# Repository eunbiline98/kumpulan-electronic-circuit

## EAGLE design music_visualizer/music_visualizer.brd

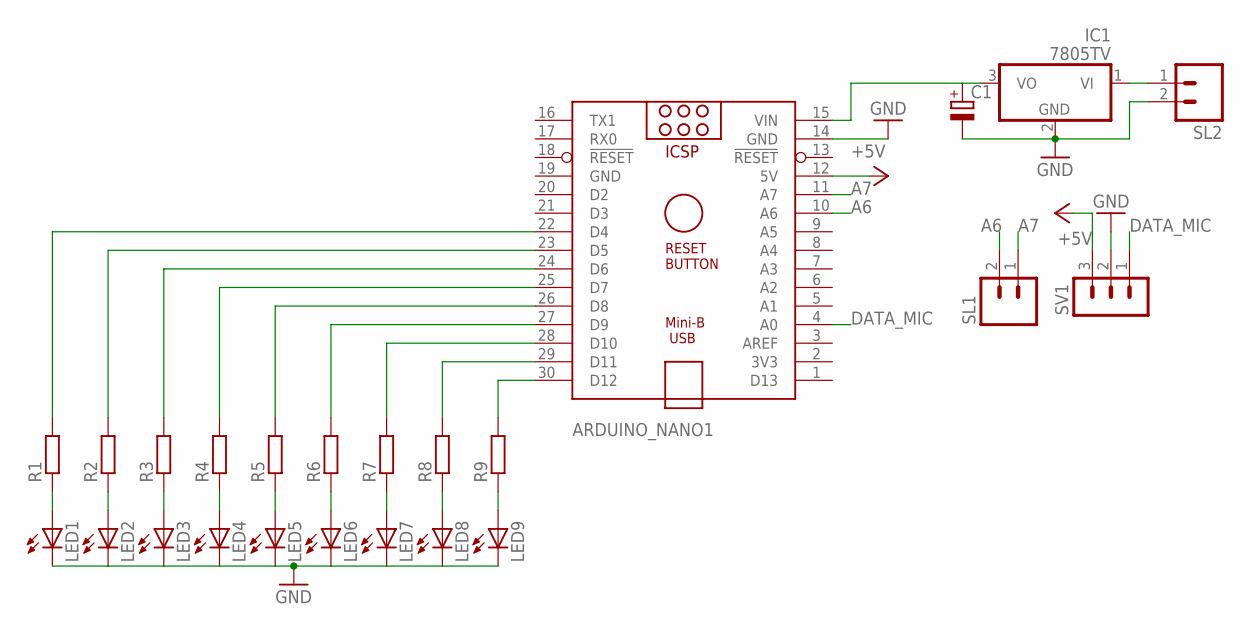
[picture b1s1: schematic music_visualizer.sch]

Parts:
ARDUINO_NANO1: ARDUINO_NANO
C1: CPOL-EUE2.5-7; E2,5-7
IC1: 7805TV; TO220V
LED1, LED2, LED3, LED4, LED5, LED6, LED7, LED8, LED9: LED5MM
R1, R2, R3, R4, R5, R6, R7, R8, R9: R-EU_0207/10; 0207/10
SL1, SL2: M02; 02P
SV1: MA03-1

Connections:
+5V: ARDUINO_NANO1.12 (5V), SV1.3
A6: ARDUINO_NANO1.10 (A6), SL1.2
A7: ARDUINO_NANO1.11 (A7), SL1.1
DATA_MIC: ARDUINO_NANO1.4 (A0), SV1.1
GND: ARDUINO_NANO1.14 (GND), ARDUINO_NANO1.19 (GND), C1.-, IC1.2 (GND), LED1.K (C), LED2.K (C), LED3.K (C), LED4.K (C), LED5.K (C), LED6.K (C), LED7.K (C), LED8.K (C), LED9.K (C), SL2.2, SV1.2
unnamed: LED1.A, R1.1
unnamed: ARDUINO_NANO1.30 (D12), R9.2
unnamed: ARDUINO_NANO1.29 (D11), R8.2
unnamed: ARDUINO_NANO1.28 (D10), R7.2
unnamed: ARDUINO_NANO1.27 (D9), R6.2
unnamed: ARDUINO_NANO1.26 (D8), R5.2
unnamed: ARDUINO_NANO1.25 (D7), R4.2
unnamed: ARDUINO_NANO1.24 (D6), R3.2
unnamed: ARDUINO_NANO1.23 (D5), R2.2
unnamed: ARDUINO_NANO1.22 (D4), R1.2
unnamed: LED2.A, R2.1
unnamed: LED3.A, R3.1
unnamed: LED4.A, R4.1
unnamed: LED5.A, R5.1
unnamed: LED6.A, R6.1
unnamed: LED7.A, R7.1
unnamed: LED8.A, R8.1
unnamed: LED9.A, R9.1
unnamed: ARDUINO_NANO1.15 (VIN), C1.+, IC1.3 (VO)
unnamed: IC1.1 (VI), SL2.1

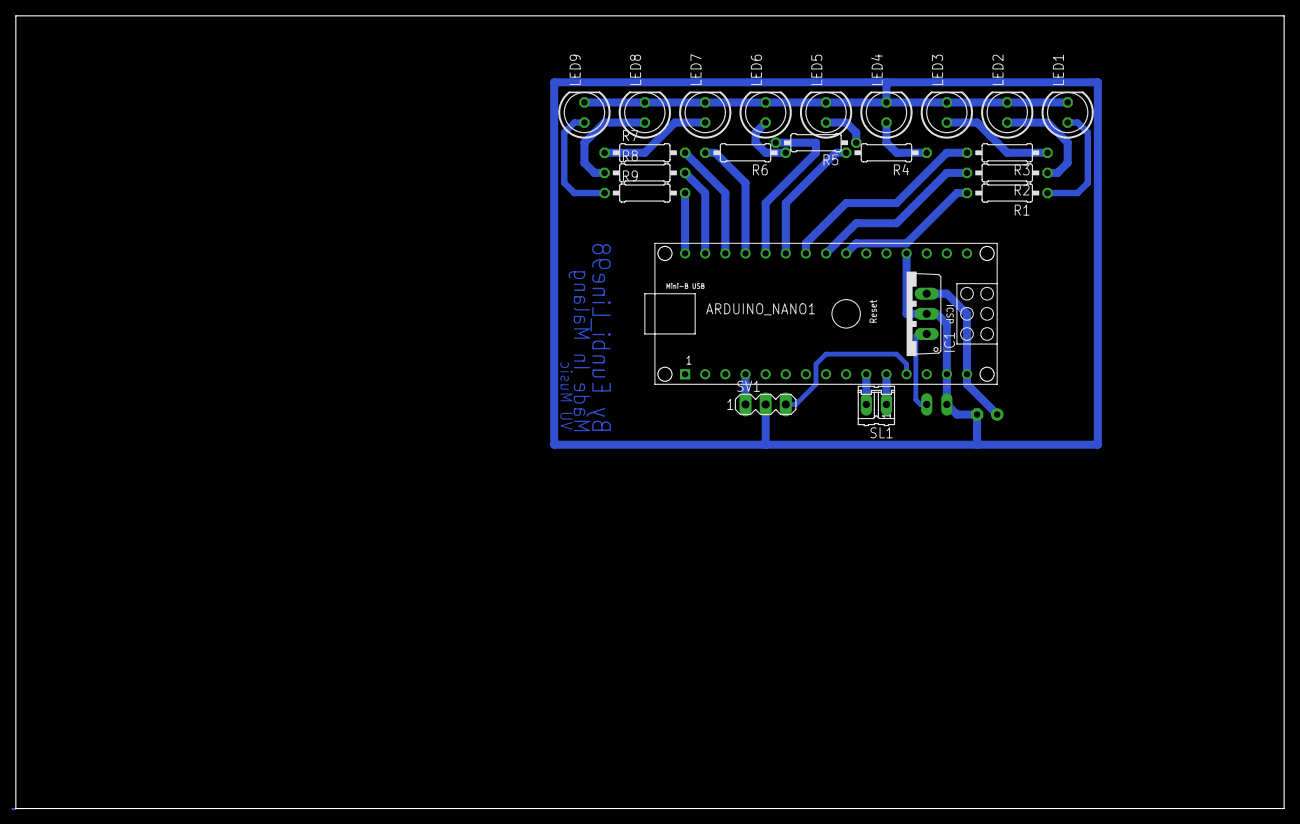
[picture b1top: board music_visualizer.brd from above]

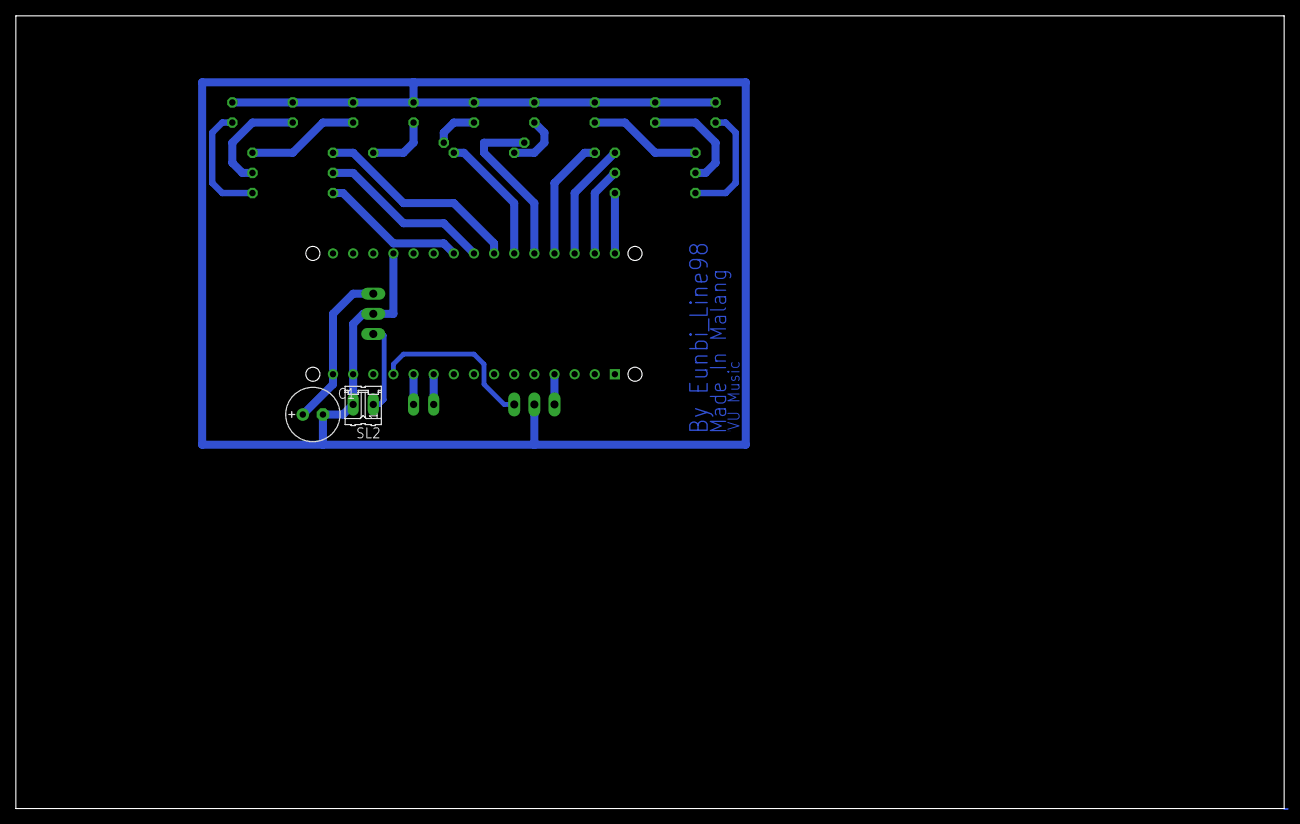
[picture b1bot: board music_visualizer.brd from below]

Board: 2 copper layers, 160.0 x 100.0 mm, 24 parts (2 on the bottom side), 25 nets.

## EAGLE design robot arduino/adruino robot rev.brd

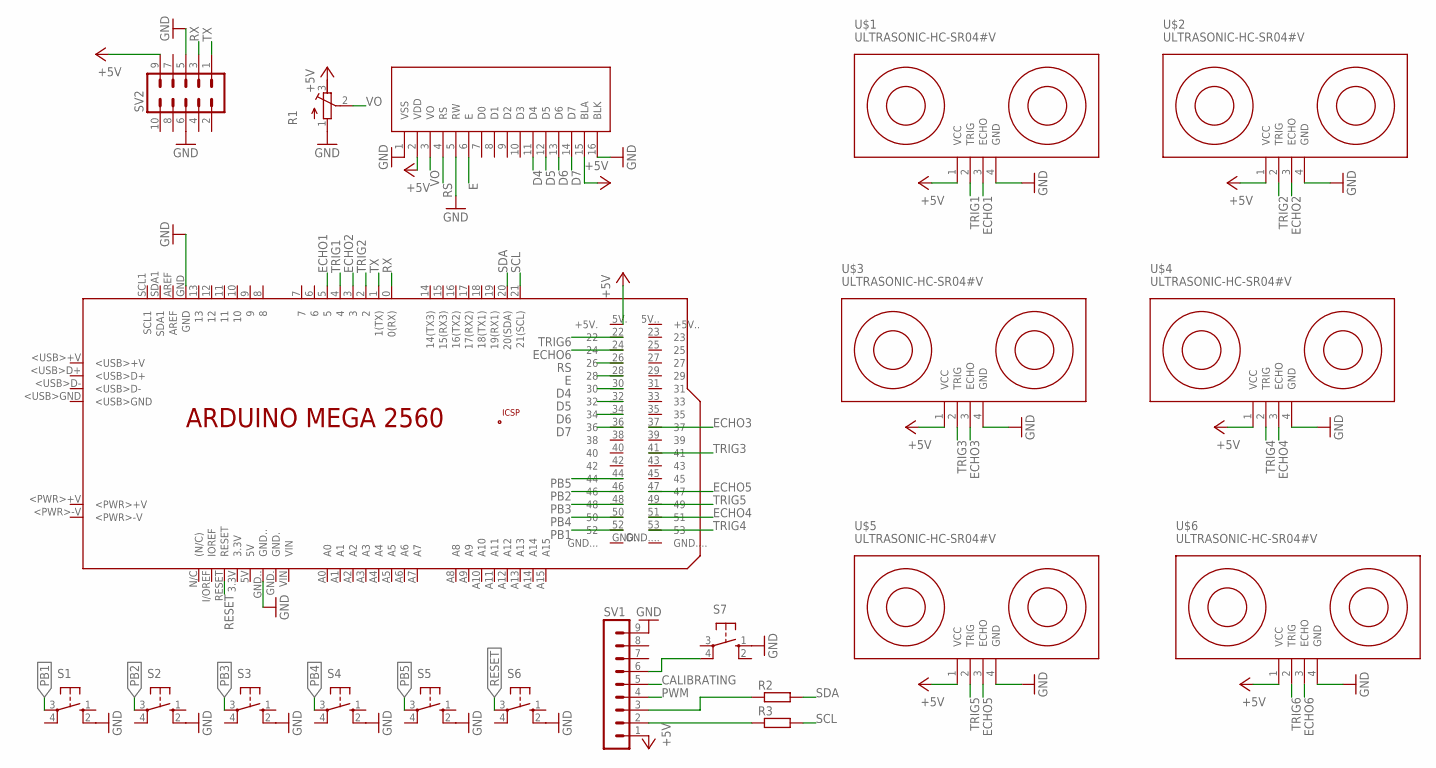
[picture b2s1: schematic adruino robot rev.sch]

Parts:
PCB1: ARDUINO_MEGA2560
R1: R-TRIMM3339P; RTRIM3339P
R2, R3: R-EU_0204/7; 0204/7
S1, S2, S3, S4, S5, S6, S7: 40-XX; B3F-40XX
SV1: MA09-1
SV2: ML10
U$1, U$2, U$3, U$4, U$5, U$6: ULTRASONIC-HC-SR04#V
U$7: 2X16LCDTOP

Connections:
+5V: PCB1.5V. (+5V.), R1.3 (E), SV1.1, SV2.9, U$1.1 (VCC), U$2.1 (VCC), U$3.1 (VCC), U$4.1 (VCC), U$5.1 (VCC), U$6.1 (VCC), U$7.2 (VDD), U$7.15 (BLA)
CALIBRATING: SV1.5
D4: PCB1.30, U$7.11 (D4)
D5: PCB1.32, U$7.12 (D5)
D6: PCB1.34, U$7.13 (D6)
D7: PCB1.36, U$7.14 (D7)
E: PCB1.28, U$7.6 (E)
ECHO1: PCB1.5, U$1.3 (ECHO)
ECHO2: PCB1.3, U$2.3 (ECHO)
ECHO3: PCB1.37, U$3.3 (ECHO)
ECHO4: PCB1.51, U$4.3 (ECHO)
ECHO5: PCB1.47, U$5.3 (ECHO)
ECHO6: PCB1.24, U$6.3 (ECHO)
GND: PCB1.GND, PCB1.GND.., R1.1 (A), S1.2 (S1), S2.2 (S1), S3.2 (S1), S4.2 (S1), S5.2 (S1), S6.2 (S1), S7.1 (S), SV1.9, SV2.5, SV2.6, U$1.4 (GND), U$2.4 (GND), U$3.4 (GND), U$4.4 (GND), U$5.4 (GND), U$6.4 (GND), U$7.1 (VSS), U$7.5 (RW), U$7.16 (BLK)
unnamed: R2.1, SV1.3
unnamed: R3.1, SV1.2
unnamed: S7.4 (P1), SV1.6
PB1: PCB1.52, S1.3
PB2: PCB1.46, S2.3
PB3: PCB1.48, S3.3
PB4: PCB1.50, S4.3
PB5: PCB1.44, S5.3
PWM: SV1.4
RESET: PCB1.RESET, S6.3
RS: PCB1.26, U$7.4 (RS)
RX: PCB1.0 (0(RX)), SV2.3
SCL: PCB1.21 (21(SCL)), R3.2
SDA: PCB1.20 (20(SDA)), R2.2
TRIG1: PCB1.4, U$1.2 (TRIG)
TRIG2: PCB1.2, U$2.2 (TRIG)
TRIG3: PCB1.41, U$3.2 (TRIG)
TRIG4: PCB1.53, U$4.2 (TRIG)
TRIG5: PCB1.49, U$5.2 (TRIG)
TRIG6: PCB1.22, U$6.2 (TRIG)
TX: PCB1.1 (1(TX)), SV2.1
VO: R1.2 (S), U$7.3 (VO)

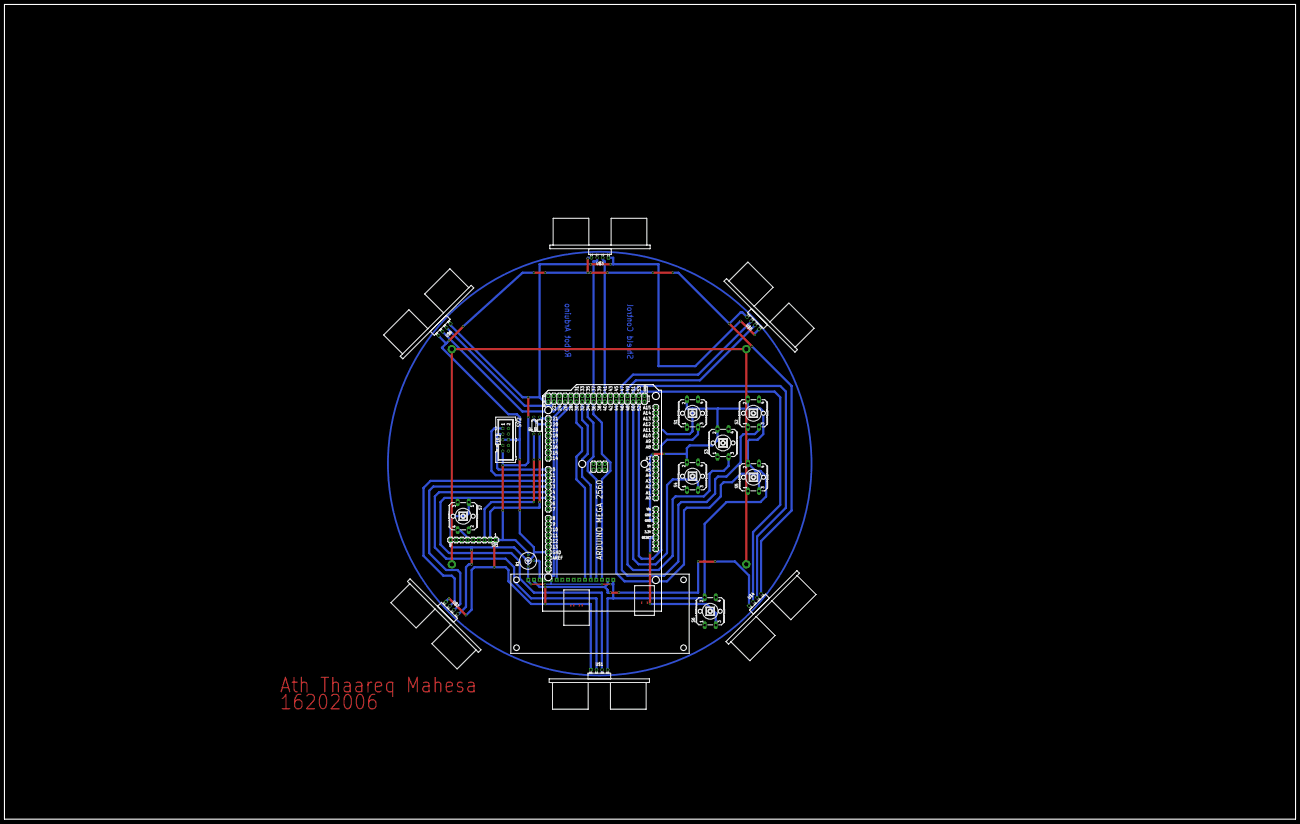
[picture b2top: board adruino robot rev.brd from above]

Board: 2 copper layers, 579.1 x 365.4 mm, 20 parts (0 on the bottom side), 34 nets.

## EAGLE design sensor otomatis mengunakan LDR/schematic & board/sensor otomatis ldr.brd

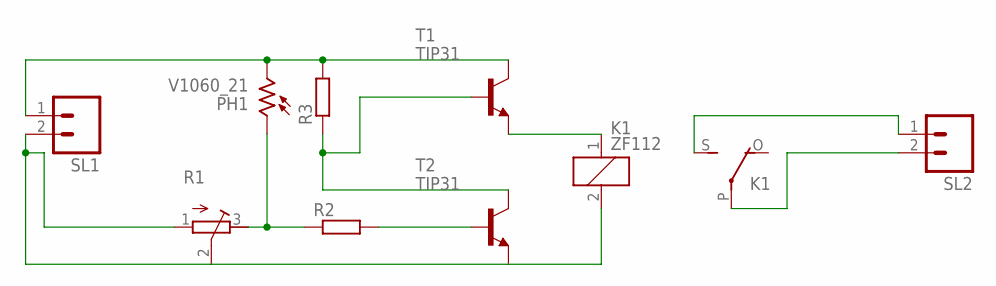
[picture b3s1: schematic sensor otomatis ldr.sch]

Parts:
K1: ZF112
PH1: V1060_21; TO-5_V10
R1: R-TRIMM3339P; RTRIM3339P
R2, R3: R-EU_0207/10; 0207/10
SL1, SL2: M02; 02P
T1, T2: TIP31; TO220

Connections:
unnamed: PH1.2, R3.2, SL1.1, T1.2 (C)
unnamed: K1.1, T1.3 (E)
unnamed: R2.2, T2.1 (B)
unnamed: PH1.1, R1.3 (E), R2.1
unnamed: R3.1, T1.1 (B), T2.2 (C)
unnamed: K1.2, R1.1 (A), R1.2 (S), SL1.2, T2.3 (E)
unnamed: K1.P, SL2.2
unnamed: K1.S, SL2.1

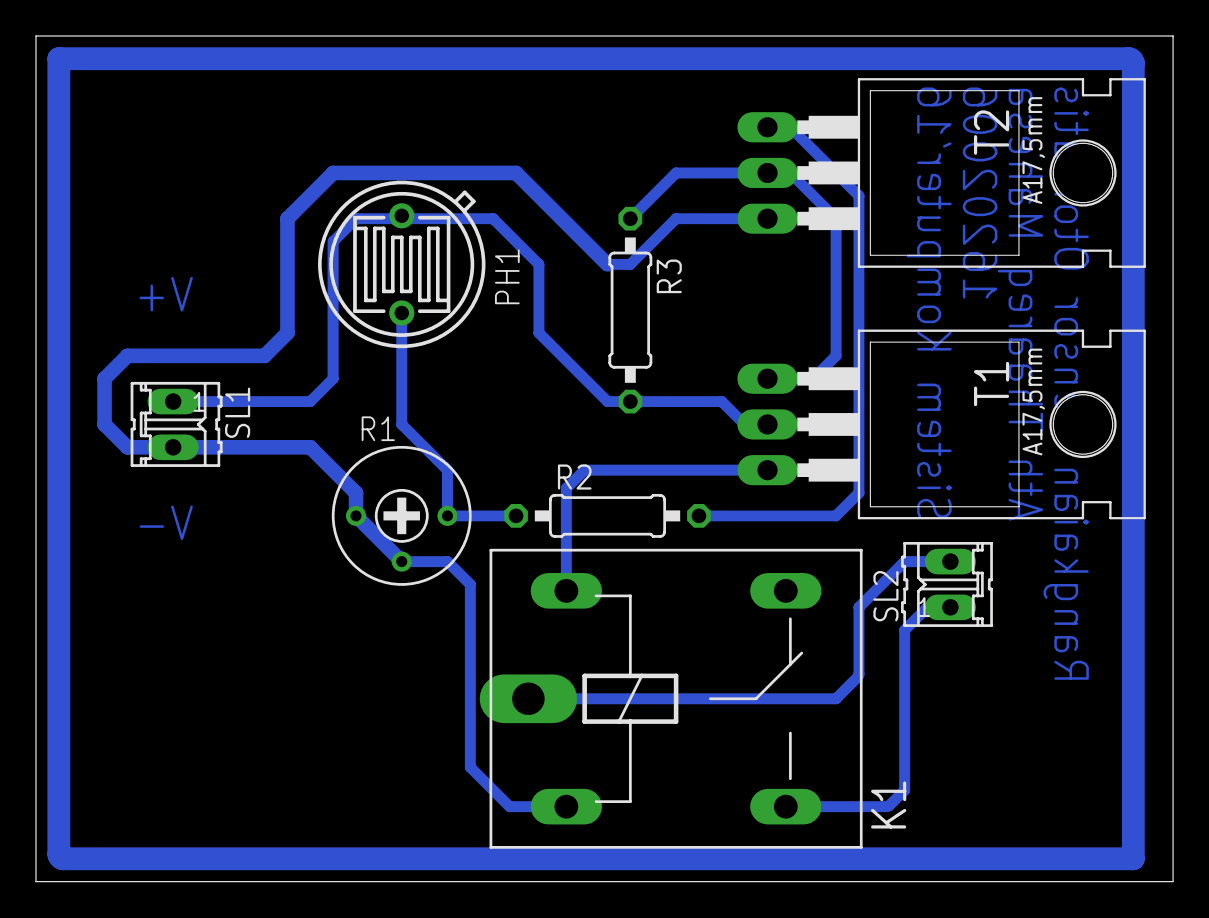
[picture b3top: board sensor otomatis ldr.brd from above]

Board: 2 copper layers, 63.2 x 47.0 mm, 9 parts (0 on the bottom side), 8 nets.

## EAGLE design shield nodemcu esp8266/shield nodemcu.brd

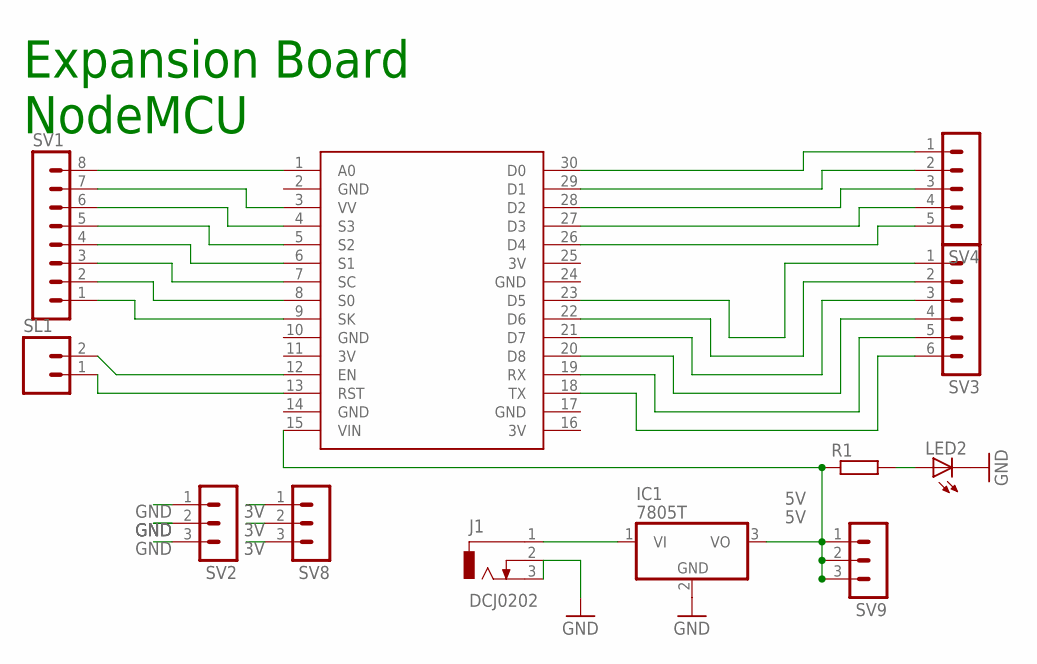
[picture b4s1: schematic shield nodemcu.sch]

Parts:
IC1: 7805T; TO220H
J1: DCJ0202
LED2: LED5MM
R1: R-EU_0207/10; 0207/10
SL1: M02; 02P
SV1: MA08-1
SV2, SV8, SV9: MA03-1
SV3: MA06-1
SV4: MA05-1
U$1: NODEMCU

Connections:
3V: SV8.1, SV8.2, SV8.3, U$1.11 (3V), U$1.16 (3V), U$1.25 (3V)
5V: IC1.3 (VO), R1.1, SV9.1, SV9.2, SV9.3, U$1.15 (VIN)
GND: IC1.2 (GND), J1.2, J1.3, LED2.K (C), SV2.1, SV2.2, SV2.3, U$1.2 (GND), U$1.10 (GND), U$1.14 (GND), U$1.17 (GND), U$1.24 (GND)
unnamed: SV4.5, U$1.26 (D4)
unnamed: SV1.8, U$1.1 (A0)
unnamed: SV1.7, U$1.3 (VV)
unnamed: SV1.6, U$1.4 (S3)
unnamed: SV1.5, U$1.5 (S2)
unnamed: LED2.A, R1.2
unnamed: SV1.3, U$1.7 (SC)
unnamed: IC1.1 (VI), J1.1
unnamed: SV1.1, U$1.9 (SK)
unnamed: SL1.1, U$1.13 (RST)
unnamed: SL1.2, U$1.12 (EN)
unnamed: SV4.1, U$1.30 (D0)
unnamed: SV4.2, U$1.29 (D1)
unnamed: SV4.3, U$1.28 (D2)
unnamed: SV4.4, U$1.27 (D3)
unnamed: SV3.1, U$1.23 (D5)
unnamed: SV3.2, U$1.22 (D6)
unnamed: SV3.3, U$1.21 (D7)
unnamed: SV3.4, U$1.20 (D8)
unnamed: SV3.5, U$1.19 (RX)
unnamed: SV3.6, U$1.18 (TX)
unnamed: SV1.4, U$1.6 (S1)
unnamed: SV1.2, U$1.8 (S0)

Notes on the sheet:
Expansion Board
NodeMCU

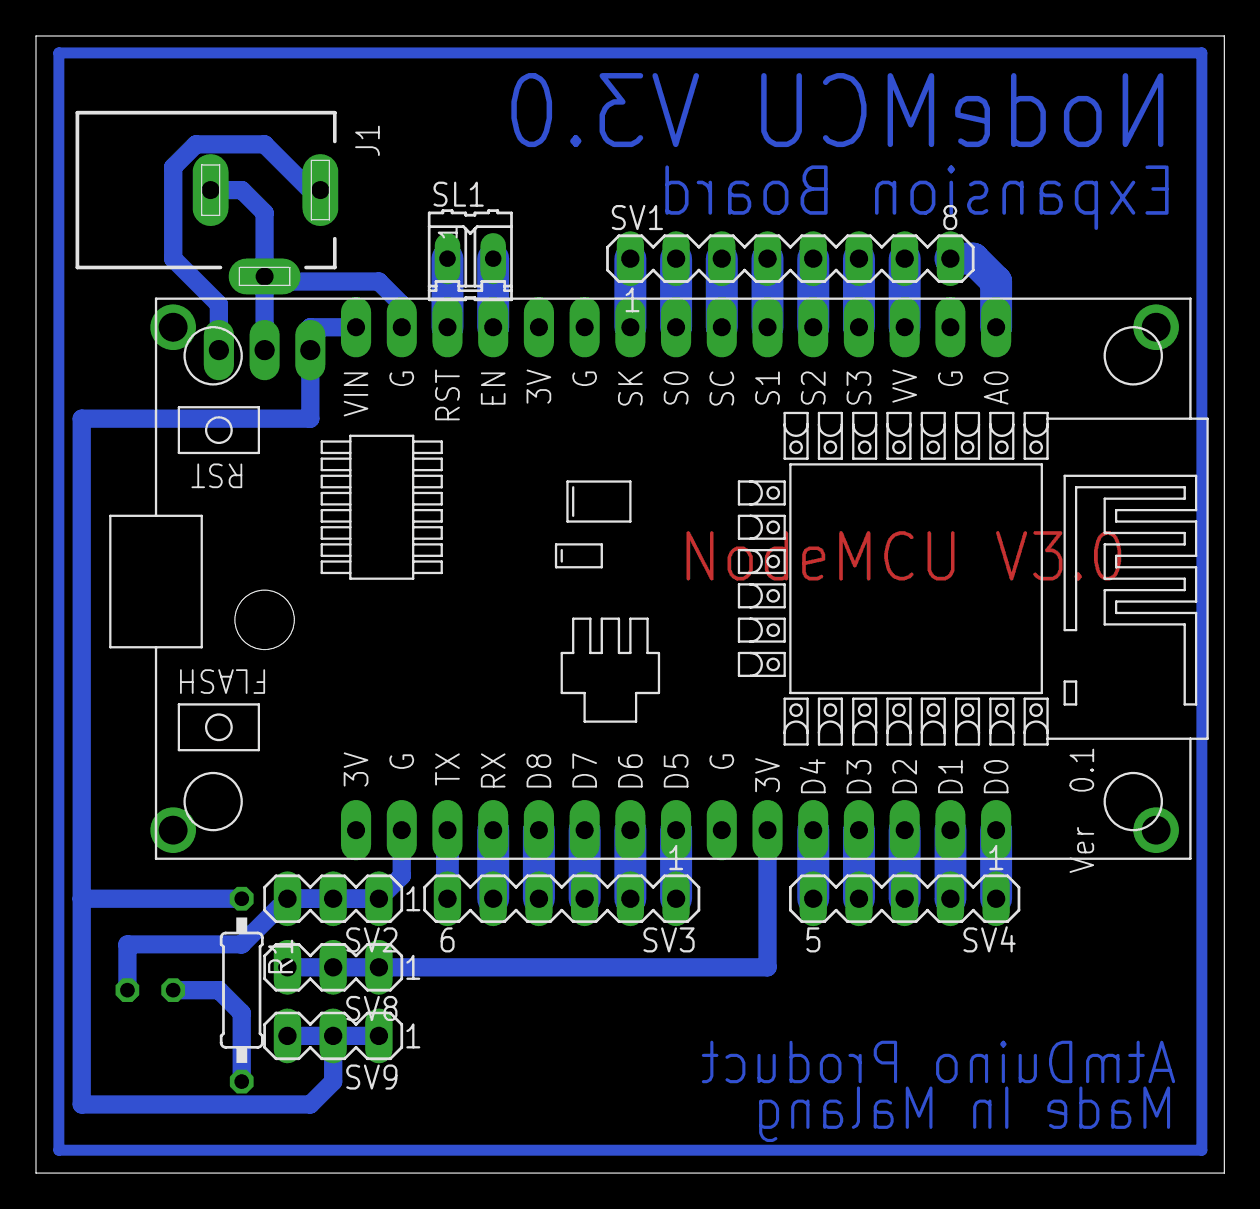
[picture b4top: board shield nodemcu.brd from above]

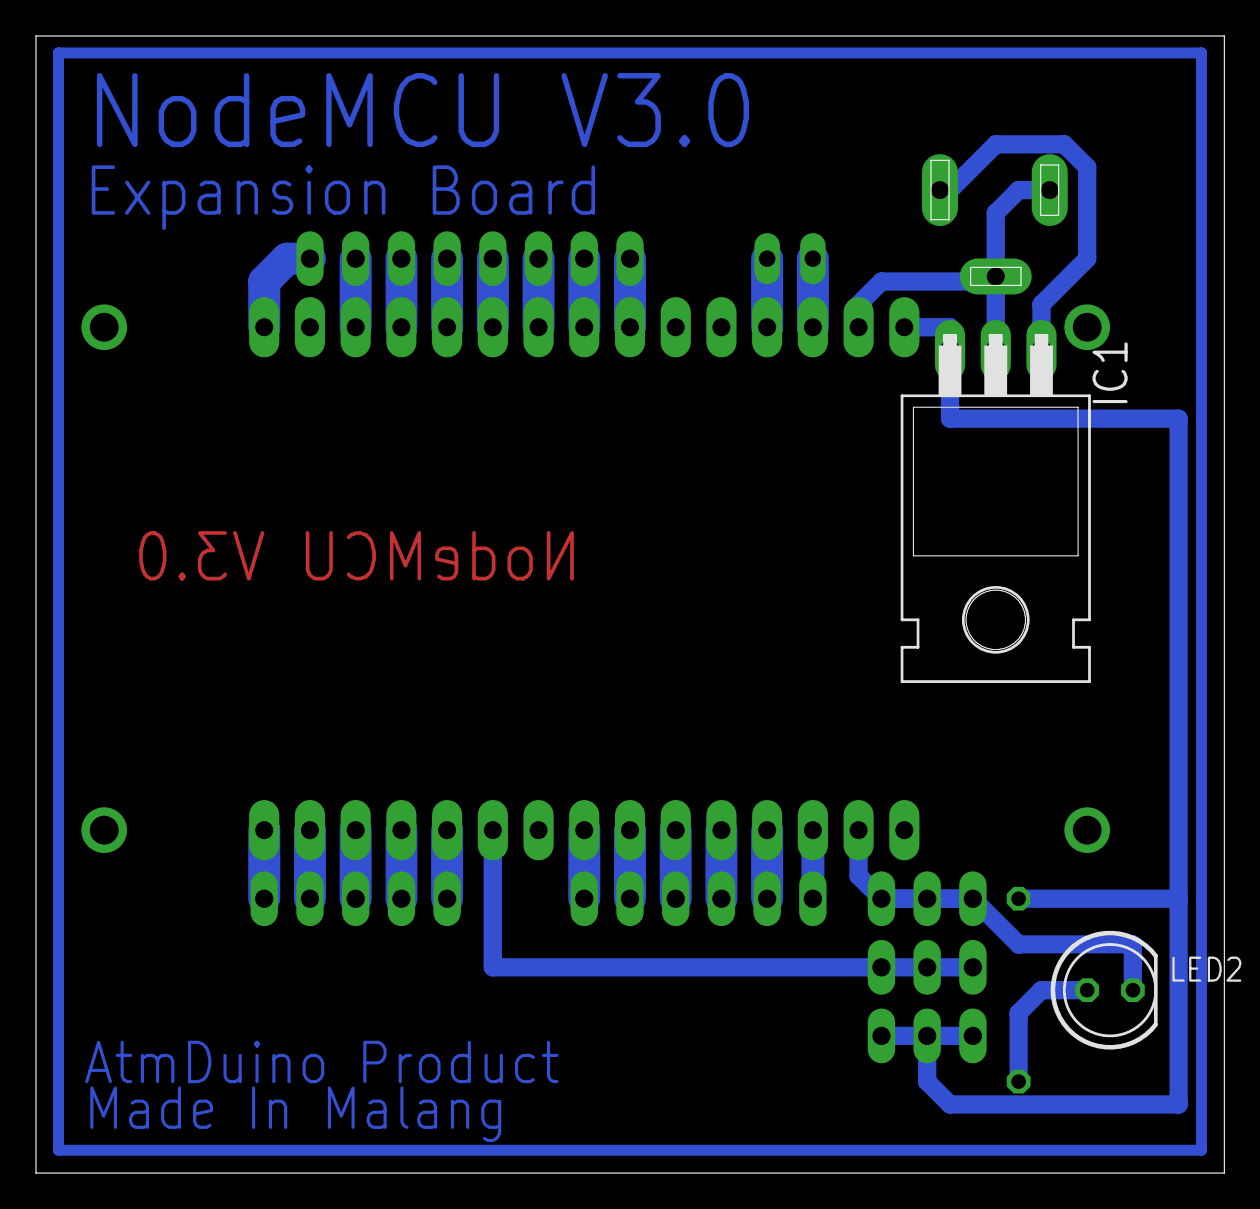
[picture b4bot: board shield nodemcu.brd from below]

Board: 2 copper layers, 66.0 x 63.2 mm, 12 parts (2 on the bottom side), 26 nets.

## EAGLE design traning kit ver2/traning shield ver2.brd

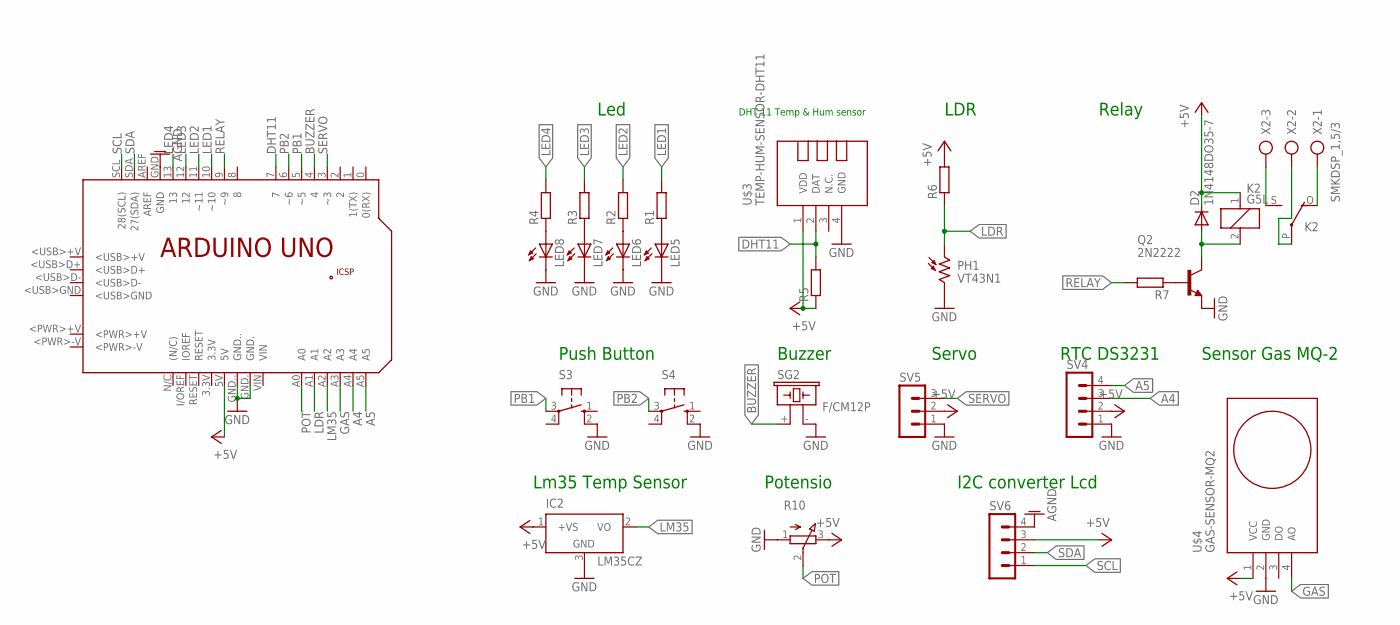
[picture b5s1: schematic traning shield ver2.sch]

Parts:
D2: 1N4148DO35-7; DO35-7
IC2: LM35CZ; TO92
K2: G5L; G5LE
LED5, LED6, LED7, LED8: LED5MM
PCB2: ARDUINO_UNO
PH1: VT43N1; VT400
Q2: 2N2222; TO18
R1, R2, R3, R4, R5, R6, R7: R-EU_0204/7; 0204/7
R10: 3RP/1610N
S3, S4: 10-XX; B3F-10XX
SG2: F/CM12P
SV4, SV6: MA04-1
SV5: MA03-1
U$3: TEMP-HUM-SENSOR-DHT11
U$4: GAS-SENSOR-MQ2
X2: SMKDSP_1,5/3

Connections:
+5V: D2.C, IC2.1 (+VS), K2.1, PCB2.5V, R5.1, R6.2, R10.3 (E), SV4.2, SV5.2, SV6.3, U$3.1 (VDD), U$4.1 (VCC)
A4: PCB2.A4, SV4.3
A5: PCB2.A5, SV4.4
AGND: PCB2.GND, SV6.4
BUZZER: PCB2.4, SG2.+ (1)
DHT11: PCB2.7, R5.2, U$3.2 (DAT)
GAS: PCB2.A3, U$4.4 (AO)
GND: IC2.3 (GND), LED5.K (C), LED6.K (C), LED7.K (C), LED8.K (C), PCB2.GND., PCB2.GND.., PH1.2, Q2.1 (E), R10.1 (A), S3.2 (S1), S4.2 (S1), SG2.- (2), SV4.1, SV5.1, U$3.4 (GND), U$4.2 (GND)
LDR: PCB2.A1, PH1.1, R6.1
LED1: PCB2.10 (~10), R1.2
LED2: PCB2.11 (~11), R2.2
LED3: PCB2.12, R3.2
LED4: PCB2.13, R4.2
LM35: IC2.2 (VO), PCB2.A2
unnamed: LED5.A, R1.1
unnamed: LED6.A, R2.1
unnamed: LED7.A, R3.1
unnamed: LED8.A, R4.1
unnamed: Q2.2 (B), R7.1
unnamed: D2.A, K2.2, Q2.3 (C)
unnamed: K2.S, X2.3
unnamed: K2.O, X2.1
unnamed: K2.P, X2.2
PB1: PCB2.5 (~5), S3.3
PB2: PCB2.6 (~6), S4.3
POT: PCB2.A0, R10.2 (S)
RELAY: PCB2.9 (~9), R7.2
SCL: PCB2.SCL (28(SCL)), SV6.1
SDA: PCB2.SDA (27(SDA)), SV6.2
SERVO: PCB2.3 (~3), SV5.3

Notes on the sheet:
Led
DHT 11 Temp & Hum sensor
LDR
Relay
Push Button
Buzzer
Servo
RTC DS3231
Sensor Gas MQ-2
I2C converter Lcd
Lm35 Temp Sensor
Potensio

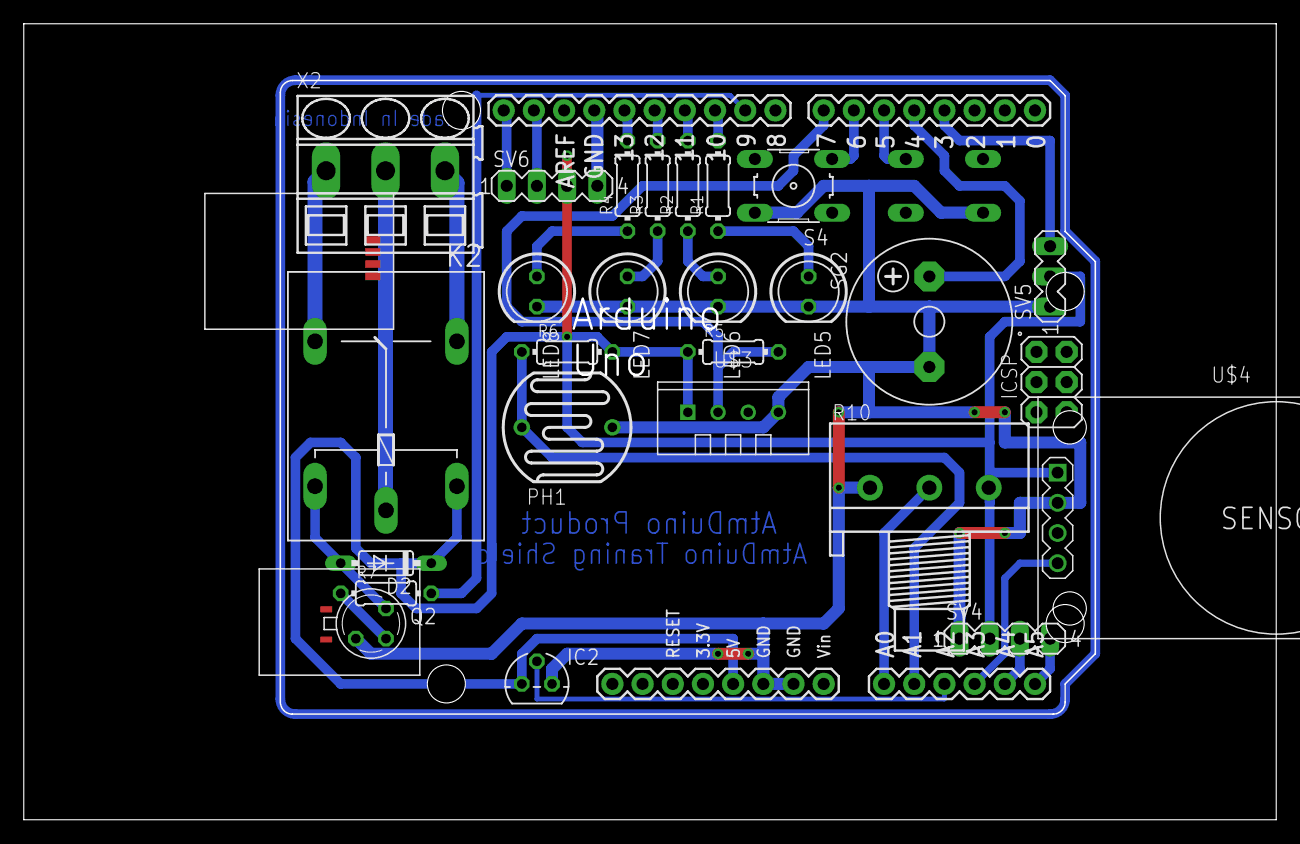
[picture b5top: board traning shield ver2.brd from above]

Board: 2 copper layers, 105.4 x 67.0 mm, 27 parts (1 on the bottom side), 30 nets.

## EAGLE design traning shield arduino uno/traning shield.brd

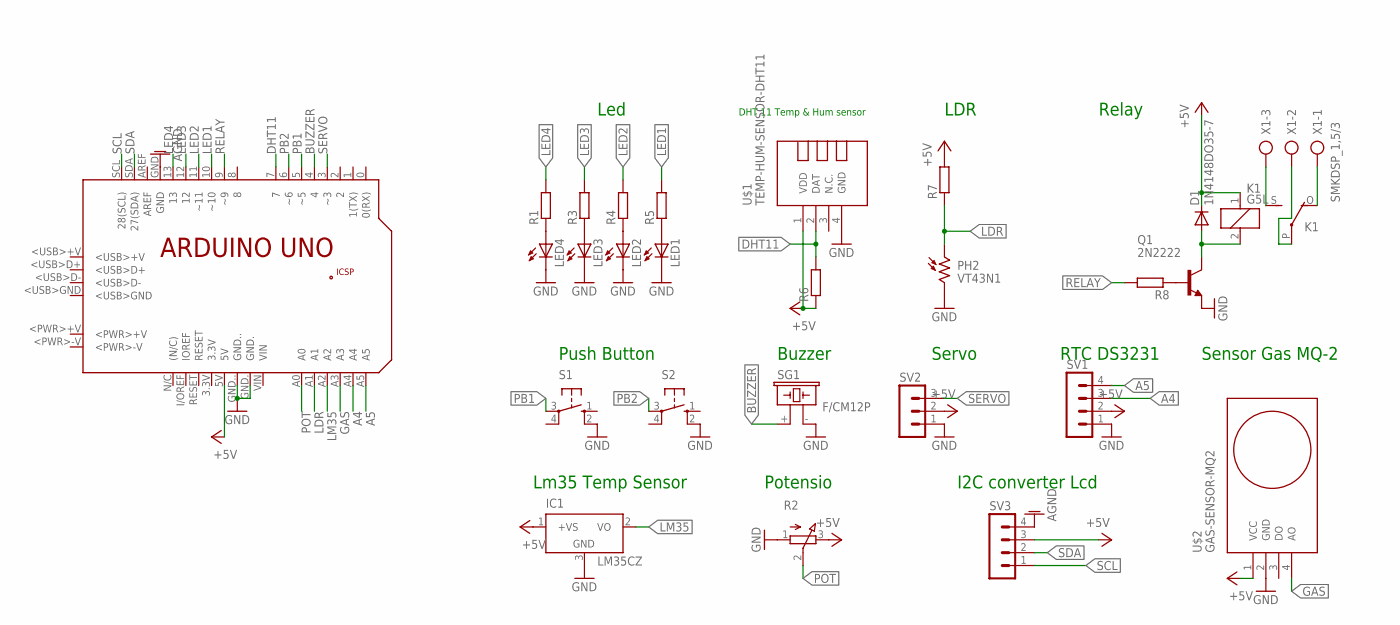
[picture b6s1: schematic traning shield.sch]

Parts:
D1: 1N4148DO35-7; DO35-7
IC1: LM35CZ; TO92
K1: G5L; G5LE
LED1, LED2, LED3, LED4: LED5MM
PCB1: ARDUINO_UNO
PH2: VT43N1; VT400
Q1: 2N2222; TO18
R1, R3, R4, R5, R6, R7, R8: R-EU_0204/5; 0204/5
R2: 3RP/1610N
S1, S2: 10-XX; B3F-10XX
SG1: F/CM12P
SV1, SV3: MA04-1
SV2: MA03-1
U$1: TEMP-HUM-SENSOR-DHT11
U$2: GAS-SENSOR-MQ2
X1: SMKDSP_1,5/3

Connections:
+5V: D1.C, IC1.1 (+VS), K1.1, PCB1.5V, R2.3 (E), R6.1, R7.2, SV1.2, SV2.2, SV3.3, U$1.1 (VDD), U$2.1 (VCC)
A4: PCB1.A4, SV1.3
A5: PCB1.A5, SV1.4
AGND: PCB1.GND, SV3.4
BUZZER: PCB1.4, SG1.+ (1)
DHT11: PCB1.7, R6.2, U$1.2 (DAT)
GAS: PCB1.A3, U$2.4 (AO)
GND: IC1.3 (GND), LED1.K (C), LED2.K (C), LED3.K (C), LED4.K (C), PCB1.GND., PCB1.GND.., PH2.2, Q1.1 (E), R2.1 (A), S1.2 (S1), S2.2 (S1), SG1.- (2), SV1.1, SV2.1, U$1.4 (GND), U$2.2 (GND)
LDR: PCB1.A1, PH2.1, R7.1
LED1: PCB1.10 (~10), R5.2
LED2: PCB1.11 (~11), R4.2
LED3: PCB1.12, R3.2
LED4: PCB1.13, R1.2
LM35: IC1.2 (VO), PCB1.A2
unnamed: LED4.A, R1.1
unnamed: LED3.A, R3.1
unnamed: LED2.A, R4.1
unnamed: LED1.A, R5.1
unnamed: Q1.2 (B), R8.1
unnamed: D1.A, K1.2, Q1.3 (C)
unnamed: K1.S, X1.3
unnamed: K1.O, X1.1
unnamed: K1.P, X1.2
PB1: PCB1.5 (~5), S1.3
PB2: PCB1.6 (~6), S2.3
POT: PCB1.A0, R2.2 (S)
RELAY: PCB1.9 (~9), R8.2
SCL: PCB1.SCL (28(SCL)), SV3.1
SDA: PCB1.SDA (27(SDA)), SV3.2
SERVO: PCB1.3 (~3), SV2.3

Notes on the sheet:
Led
DHT 11 Temp & Hum sensor
LDR
Relay
Push Button
Buzzer
Servo
RTC DS3231
Sensor Gas MQ-2
I2C converter Lcd
Lm35 Temp Sensor
Potensio

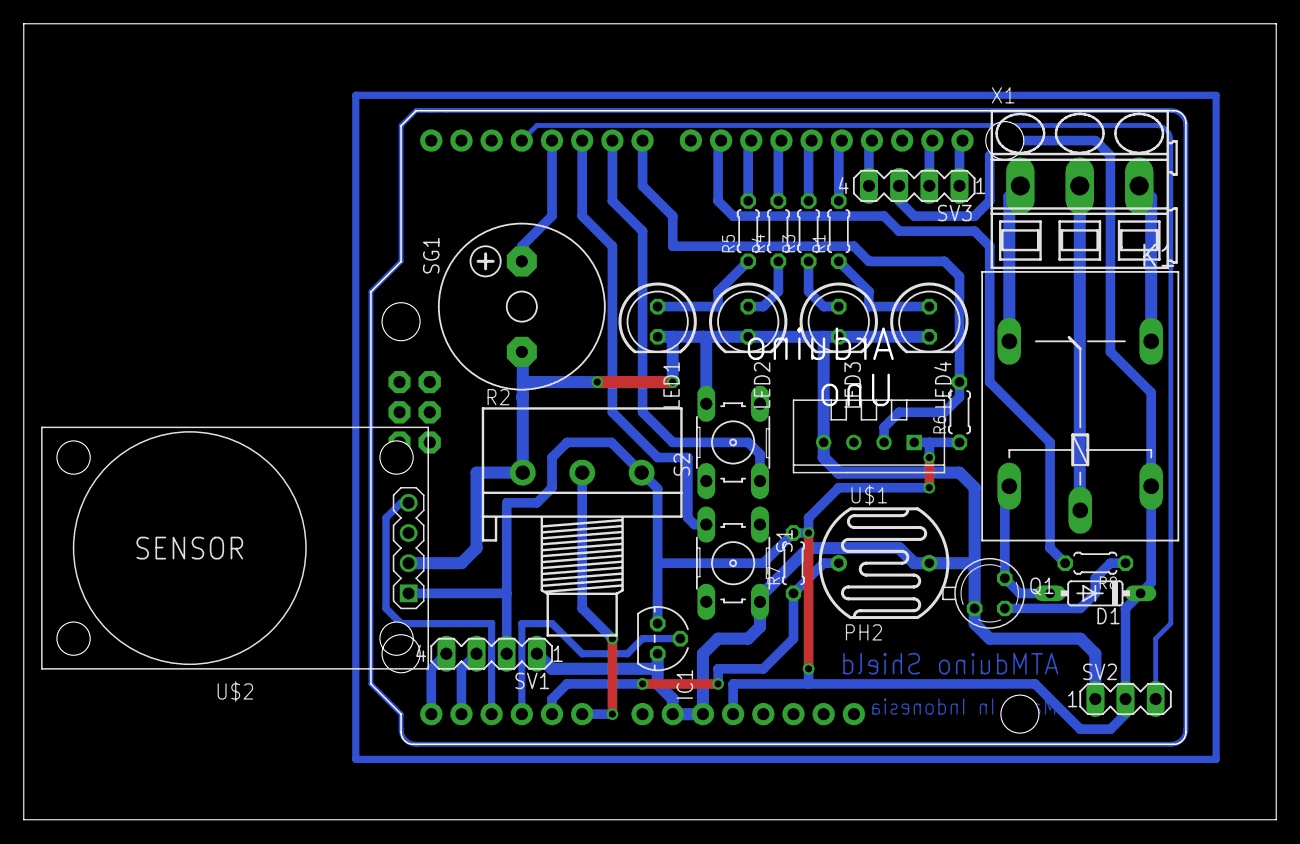
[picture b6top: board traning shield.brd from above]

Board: 2 copper layers, 105.4 x 67.0 mm, 27 parts (1 on the bottom side), 30 nets.

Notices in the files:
parts and their libraries:
diy-modules: Released under the Creative Commons Attribution 4.0 International License: http://creativecommons.org/licenses/by/4.0
